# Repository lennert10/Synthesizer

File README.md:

# Synthesizer
Analog synthesizer top level repository

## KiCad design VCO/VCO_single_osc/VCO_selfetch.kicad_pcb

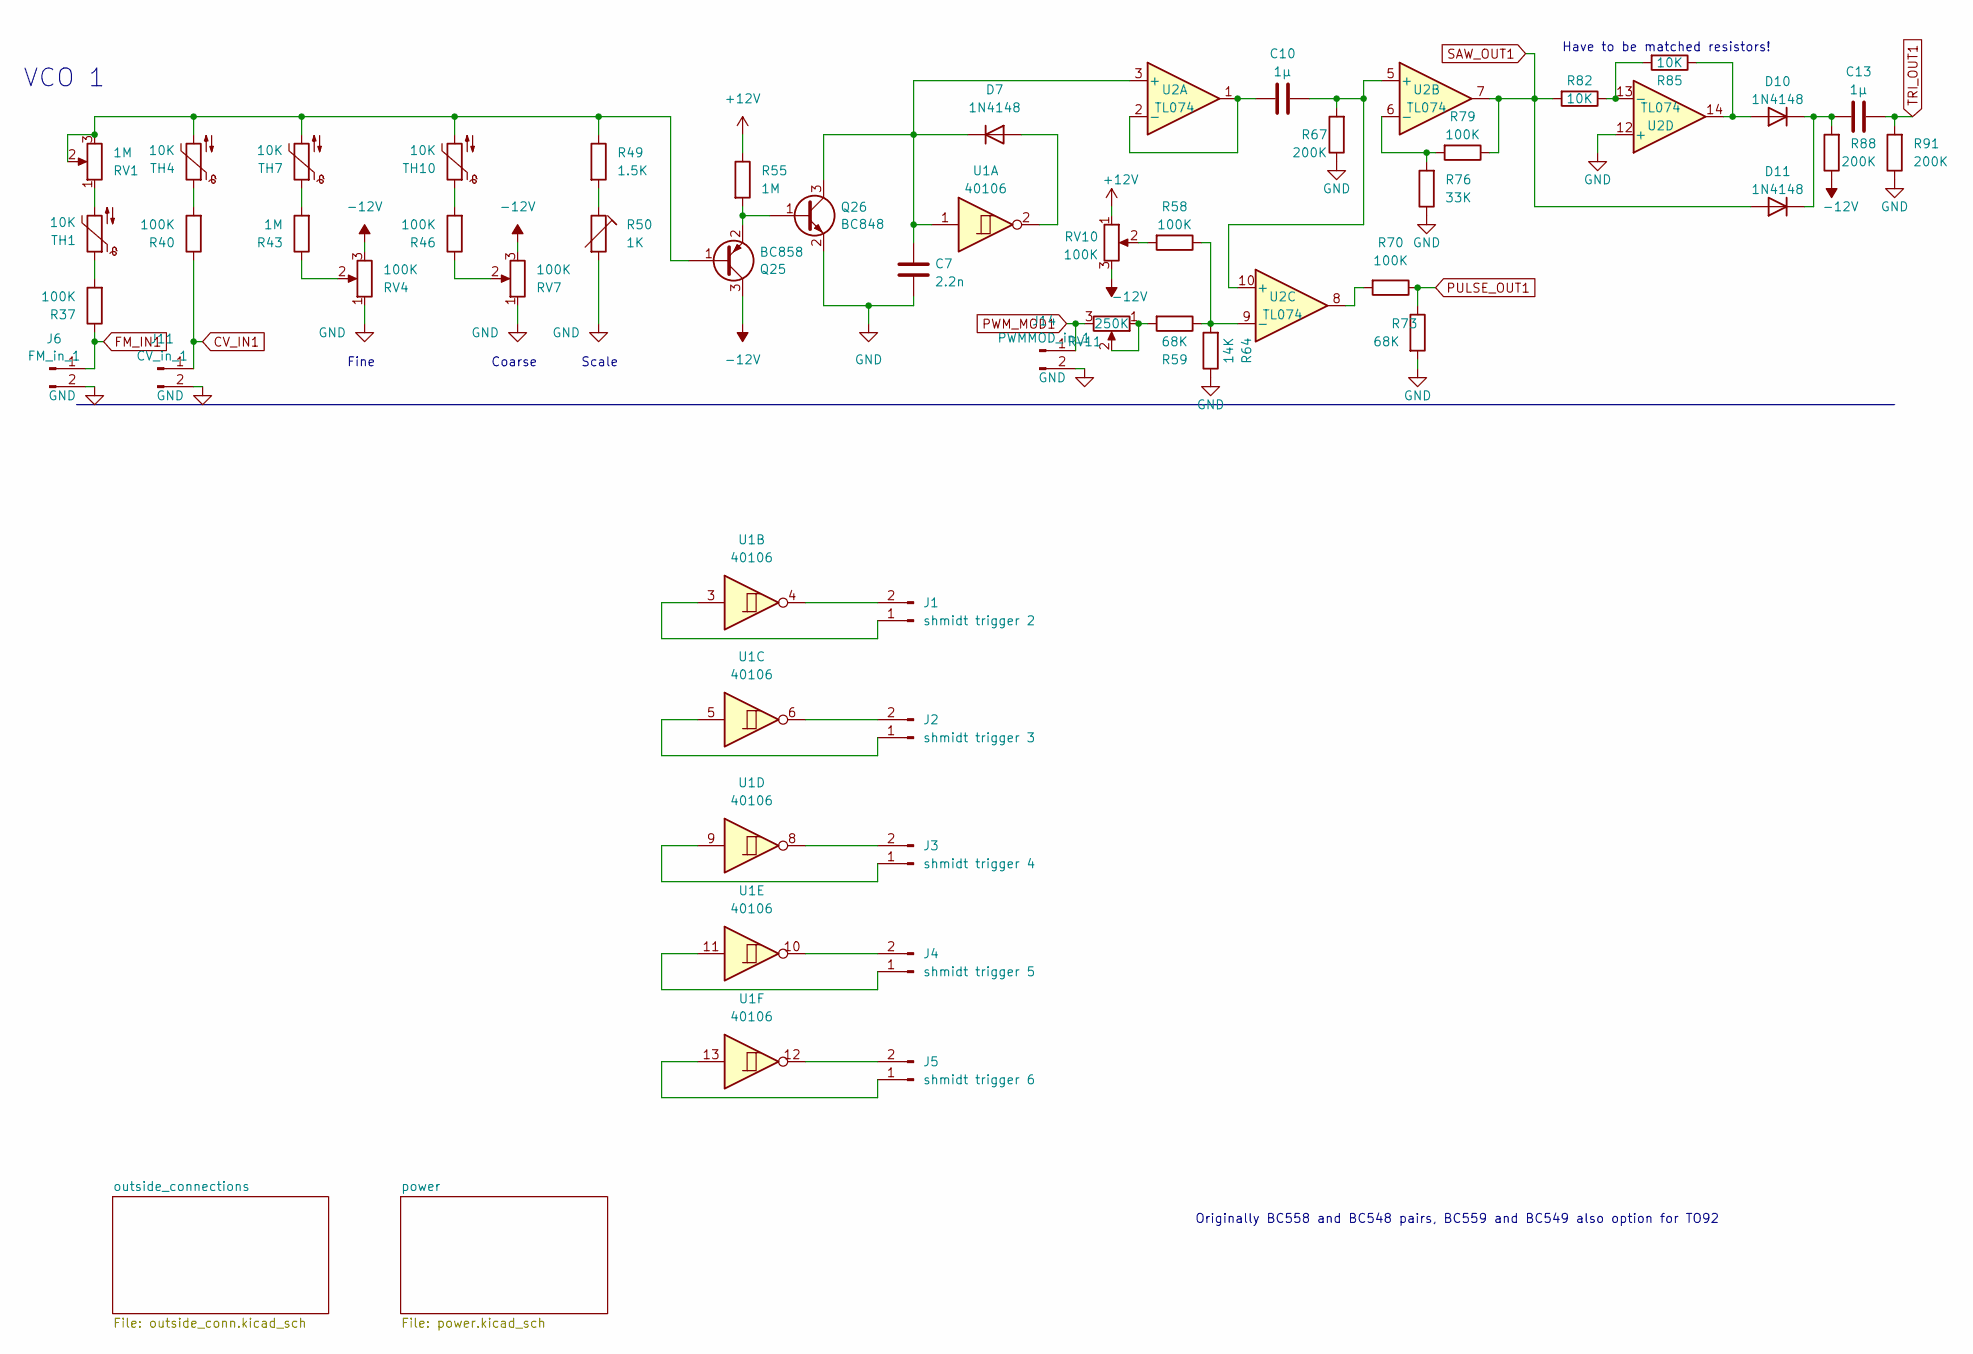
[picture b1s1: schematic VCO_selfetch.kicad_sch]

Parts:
C7: 2.2n; C_0402_1005Metric_Pad0.74x0.62mm_HandSolder
C10, C13: 1µ; C_0402_1005Metric_Pad0.74x0.62mm_HandSolder
D7, D10, D11: 1N4148; D_SOD-123
J1: shmidt trigger 2; PinHeader_1x02_P2.00mm_Vertical
J2: shmidt trigger 3; PinHeader_1x02_P2.00mm_Vertical
J3: shmidt trigger 4; PinHeader_1x02_P2.00mm_Vertical
J4: shmidt trigger 5; PinHeader_1x02_P2.00mm_Vertical
J5: shmidt trigger 6; PinHeader_1x02_P2.00mm_Vertical
J6: FM_in_1; PinHeader_1x02_P2.54mm_Vertical
J11: CV_in_1; PinHeader_1x02_P2.54mm_Vertical
J14: PWMMOD_in_1; PinHeader_1x02_P2.54mm_Vertical
Q25: BC858; SOT-23
Q26: BC848; SOT-23
R37, R40, R46, R58, R70, R79: 100K; R_0603_1608Metric_Pad0.98x0.95mm_HandSolder
R43, R55: 1M; R_0603_1608Metric_Pad0.98x0.95mm_HandSolder
R49: 1.5K; R_0603_1608Metric_Pad0.98x0.95mm_HandSolder
R50: 1K; Potentiometer_Bourns_3296W_Vertical
R59, R73: 68K; R_0603_1608Metric_Pad0.98x0.95mm_HandSolder
R64: 14K; R_0603_1608Metric_Pad0.98x0.95mm_HandSolder
R67, R88, R91: 200K; R_0603_1608Metric_Pad0.98x0.95mm_HandSolder
R76: 33K; R_0603_1608Metric_Pad0.98x0.95mm_HandSolder
R82, R85: 10K; R_0603_1608Metric_Pad0.98x0.95mm_HandSolder
RV1: 1M; PinHeader_1x03_P2.54mm_Vertical
RV4, RV7, RV10: 100K; PinHeader_1x03_P2.54mm_Vertical
RV11: 250K; PinHeader_1x03_P2.54mm_Vertical
TH1, TH4, TH7, TH10: 10K; R_0603_1608Metric_Pad0.98x0.95mm_HandSolder
U1: 40106; DIP-14_W7.62mm_Socket
U2: TL074; DIP-14_W7.62mm_Socket

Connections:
+12V: R55.1, RV10.1; also elsewhere on the board
-12V: Q25.3 (C), R88.1, RV4.3, RV7.3, RV10.3; also elsewhere on the board
CV_IN1: J11.1, R40.1
FM_IN1: J6.1, R37.1
GND: C7.1, J6.2, J11.2, J14.2, Q26.2 (E), R50.2, R64.1, R67.1, R73.2, R76.1, R91.1, RV4.1, RV7.1, U2.12 (+); also elsewhere on the board
unnamed: D7.2 (A), U1.2
unnamed: C7.2, D7.1 (K), Q26.3 (C), U1.1, U2.3 (+)
unnamed: D10.2 (A), R85.1, U2.14
unnamed: C13.2, D10.1 (K), D11.1 (K), R88.2
unnamed: J1.1, U1.3
unnamed: J1.2, U1.4
unnamed: J2.1, U1.5
unnamed: J2.2, U1.6
unnamed: J3.1, U1.9
unnamed: J3.2, U1.8
unnamed: J4.1, U1.11
unnamed: J4.2, U1.10
unnamed: J5.1, U1.13
unnamed: J5.2, U1.12
unnamed: Q25.1 (B), R49.1, RV1.2, RV1.3, TH4.2, TH7.2, TH10.2
unnamed: Q25.2 (E), Q26.1 (B), R55.2
unnamed: R37.2, TH1.1
unnamed: R40.2, TH4.1
unnamed: R43.1, RV4.2
unnamed: R43.2, TH7.1
unnamed: R46.1, RV7.2
unnamed: R46.2, TH10.1
unnamed: R49.2, R50.1
unnamed: R58.2, RV10.2
unnamed: R59.2, RV11.1, RV11.2
unnamed: R70.2, U2.8
unnamed: RV1.1, TH1.2
unnamed: C10.2, U2.1, U2.2 (-)
unnamed: C10.1, R67.2, U2.5 (+), U2.10 (+)
unnamed: R76.2, R79.2, U2.6 (-)
unnamed: R58.1, R59.1, R64.2, U2.9 (-)
unnamed: R82.1, R85.2, U2.13 (-)
PULSE_OUT1: R70.1, R73.1; also elsewhere on the board
PWM_MOD1: J14.1, RV11.3
SAW_OUT1: D11.2 (A), R79.1, R82.2, U2.7; also elsewhere on the board
TRI_OUT1: C13.1, R91.2; also elsewhere on the board

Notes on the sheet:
Have to be matched resistors!
Fine
VCO 1
Coarse
Scale
Originally BC558 and BC548 pairs, BC559 and BC549 also option for TO92

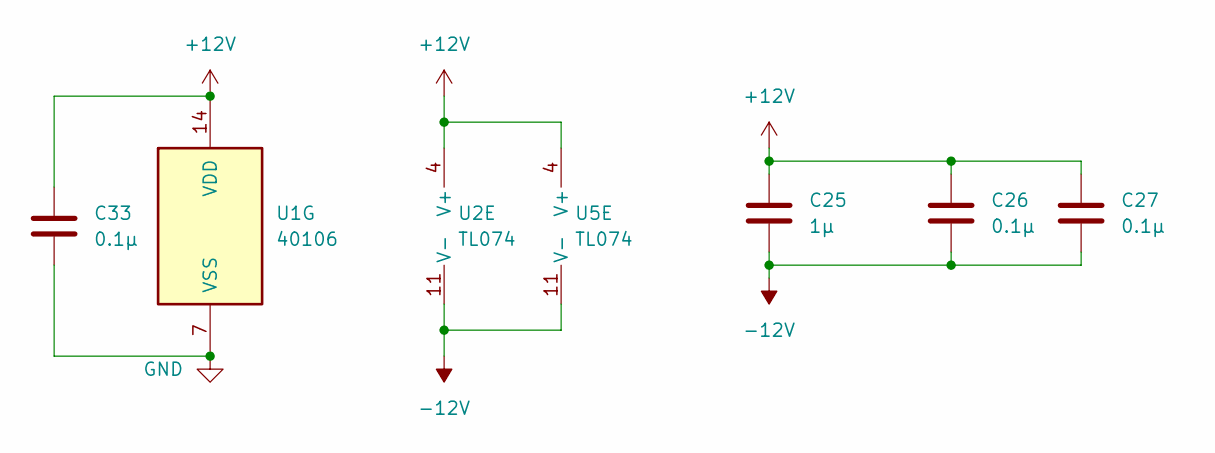
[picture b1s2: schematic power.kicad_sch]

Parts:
C25: 1µ; C_0402_1005Metric_Pad0.74x0.62mm_HandSolder
C26, C27, C33: 0.1µ; C_0603_1608Metric_Pad1.08x0.95mm_HandSolder
U1: 40106; DIP-14_W7.62mm_Socket
U2, U5: TL074; DIP-14_W7.62mm_Socket

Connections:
+12V: C25.2, C26.2, C27.2, C33.2, U1.14 (VDD), U2.4 (V+), U5.4 (V+); also elsewhere on the board
-12V: C25.1, C26.1, C27.1, U2.11 (V-), U5.11 (V-); also elsewhere on the board
GND: C33.1, U1.7 (VSS); also elsewhere on the board

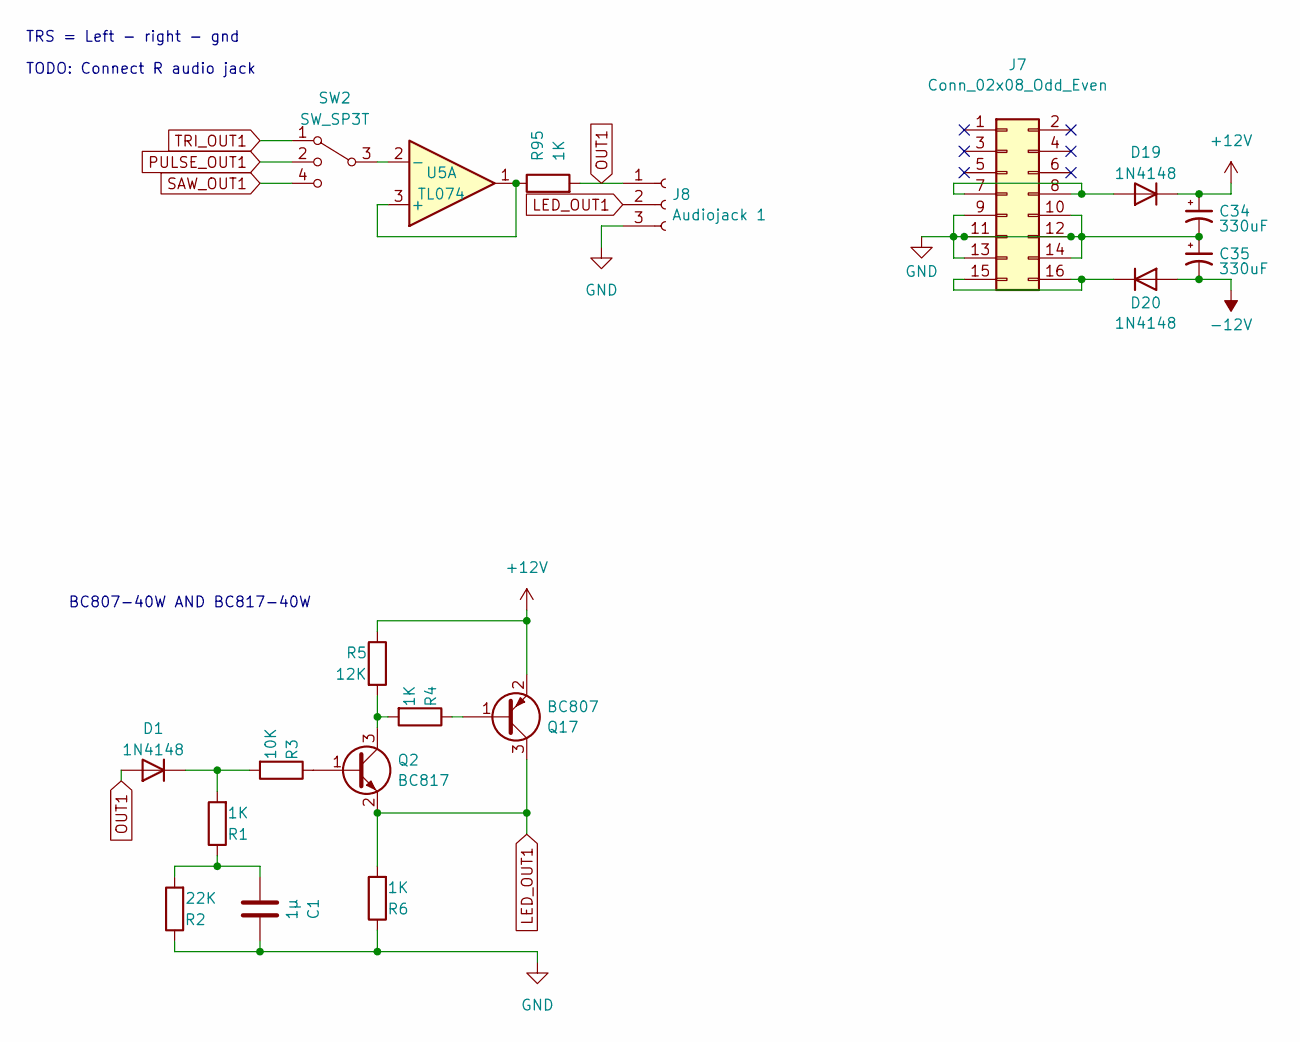
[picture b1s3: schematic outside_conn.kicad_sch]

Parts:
C1: 1µ; C_0402_1005Metric_Pad0.74x0.62mm_HandSolder
C34, C35: 330uF; CP_Radial_D12.5mm_P7.50mm
D1, D19, D20: 1N4148; D_SOD-123
J7: Conn_02x08_Odd_Even; PinHeader_2x08_P2.54mm_Vertical
J8: Audiojack 1; PinHeader_1x03_P2.54mm_Vertical
Q2: BC817; SOT-23
Q17: BC807; SOT-23
R1, R4, R6, R95: 1K; R_0603_1608Metric_Pad0.98x0.95mm_HandSolder
R2: 22K; R_0603_1608Metric_Pad0.98x0.95mm_HandSolder
R3: 10K; R_0603_1608Metric_Pad0.98x0.95mm_HandSolder
R5: 12K; R_0603_1608Metric_Pad0.98x0.95mm_HandSolder
SW2: SW_SP3T; PinHeader_1x04_P2.54mm_Vertical
U5: TL074; DIP-14_W7.62mm_Socket

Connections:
+12V: C34.1, D19.1 (K), Q17.2 (E), R5.1; also elsewhere on the board
-12V: C35.2, D20.2 (A); also elsewhere on the board
GND: C1.1, C34.2, C35.1, J7.9, J7.10, J7.11, J7.12, J7.13, J7.14, J8.3, R2.1, R6.1; also elsewhere on the board
LED_OUT1: J8.2, Q2.2 (E), Q17.3 (C), R6.2
unnamed: C1.2, R1.1, R2.2
unnamed: D1.1 (K), R1.2, R3.2
unnamed: D19.2 (A), J7.7, J7.8
unnamed: D20.1 (K), J7.15, J7.16
unnamed: Q2.1 (B), R3.1
unnamed: Q2.3 (C), R4.2, R5.2
unnamed: Q17.1 (B), R4.1
unnamed: R95.1, U5.1, U5.3 (+)
unnamed: SW2.3, U5.2 (-)
OUT1: D1.2 (A), J8.1, R95.2
PULSE_OUT1: SW2.2; also elsewhere on the board
SAW_OUT1: SW2.4; also elsewhere on the board
TRI_OUT1: SW2.1; also elsewhere on the board

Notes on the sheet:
TRS = Left - right - gnd
BC807-40W AND BC817-40W
TODO: Connect R audio jack

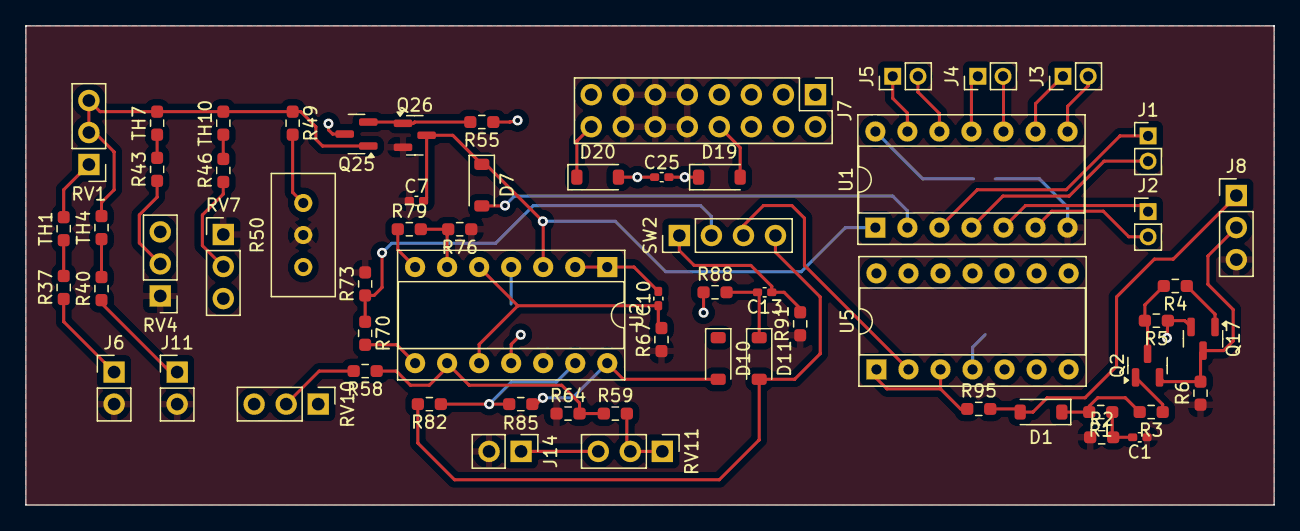
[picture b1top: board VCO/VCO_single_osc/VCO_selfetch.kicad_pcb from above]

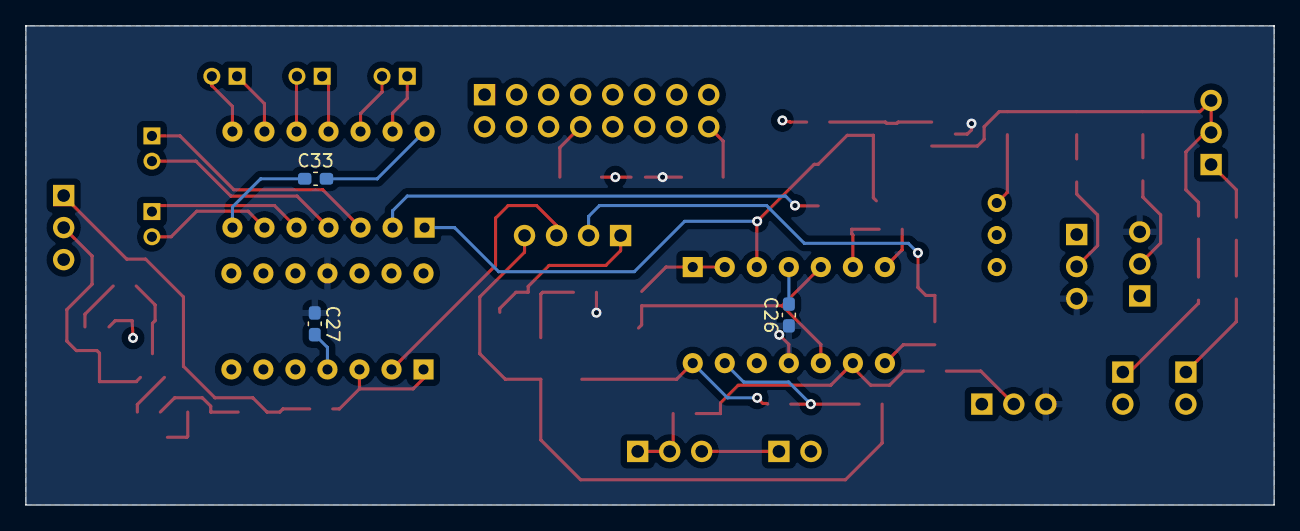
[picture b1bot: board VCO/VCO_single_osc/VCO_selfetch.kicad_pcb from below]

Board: 4 copper layers, 99.0 x 38.0 mm, 67 parts (3 on the bottom side), 52 nets.

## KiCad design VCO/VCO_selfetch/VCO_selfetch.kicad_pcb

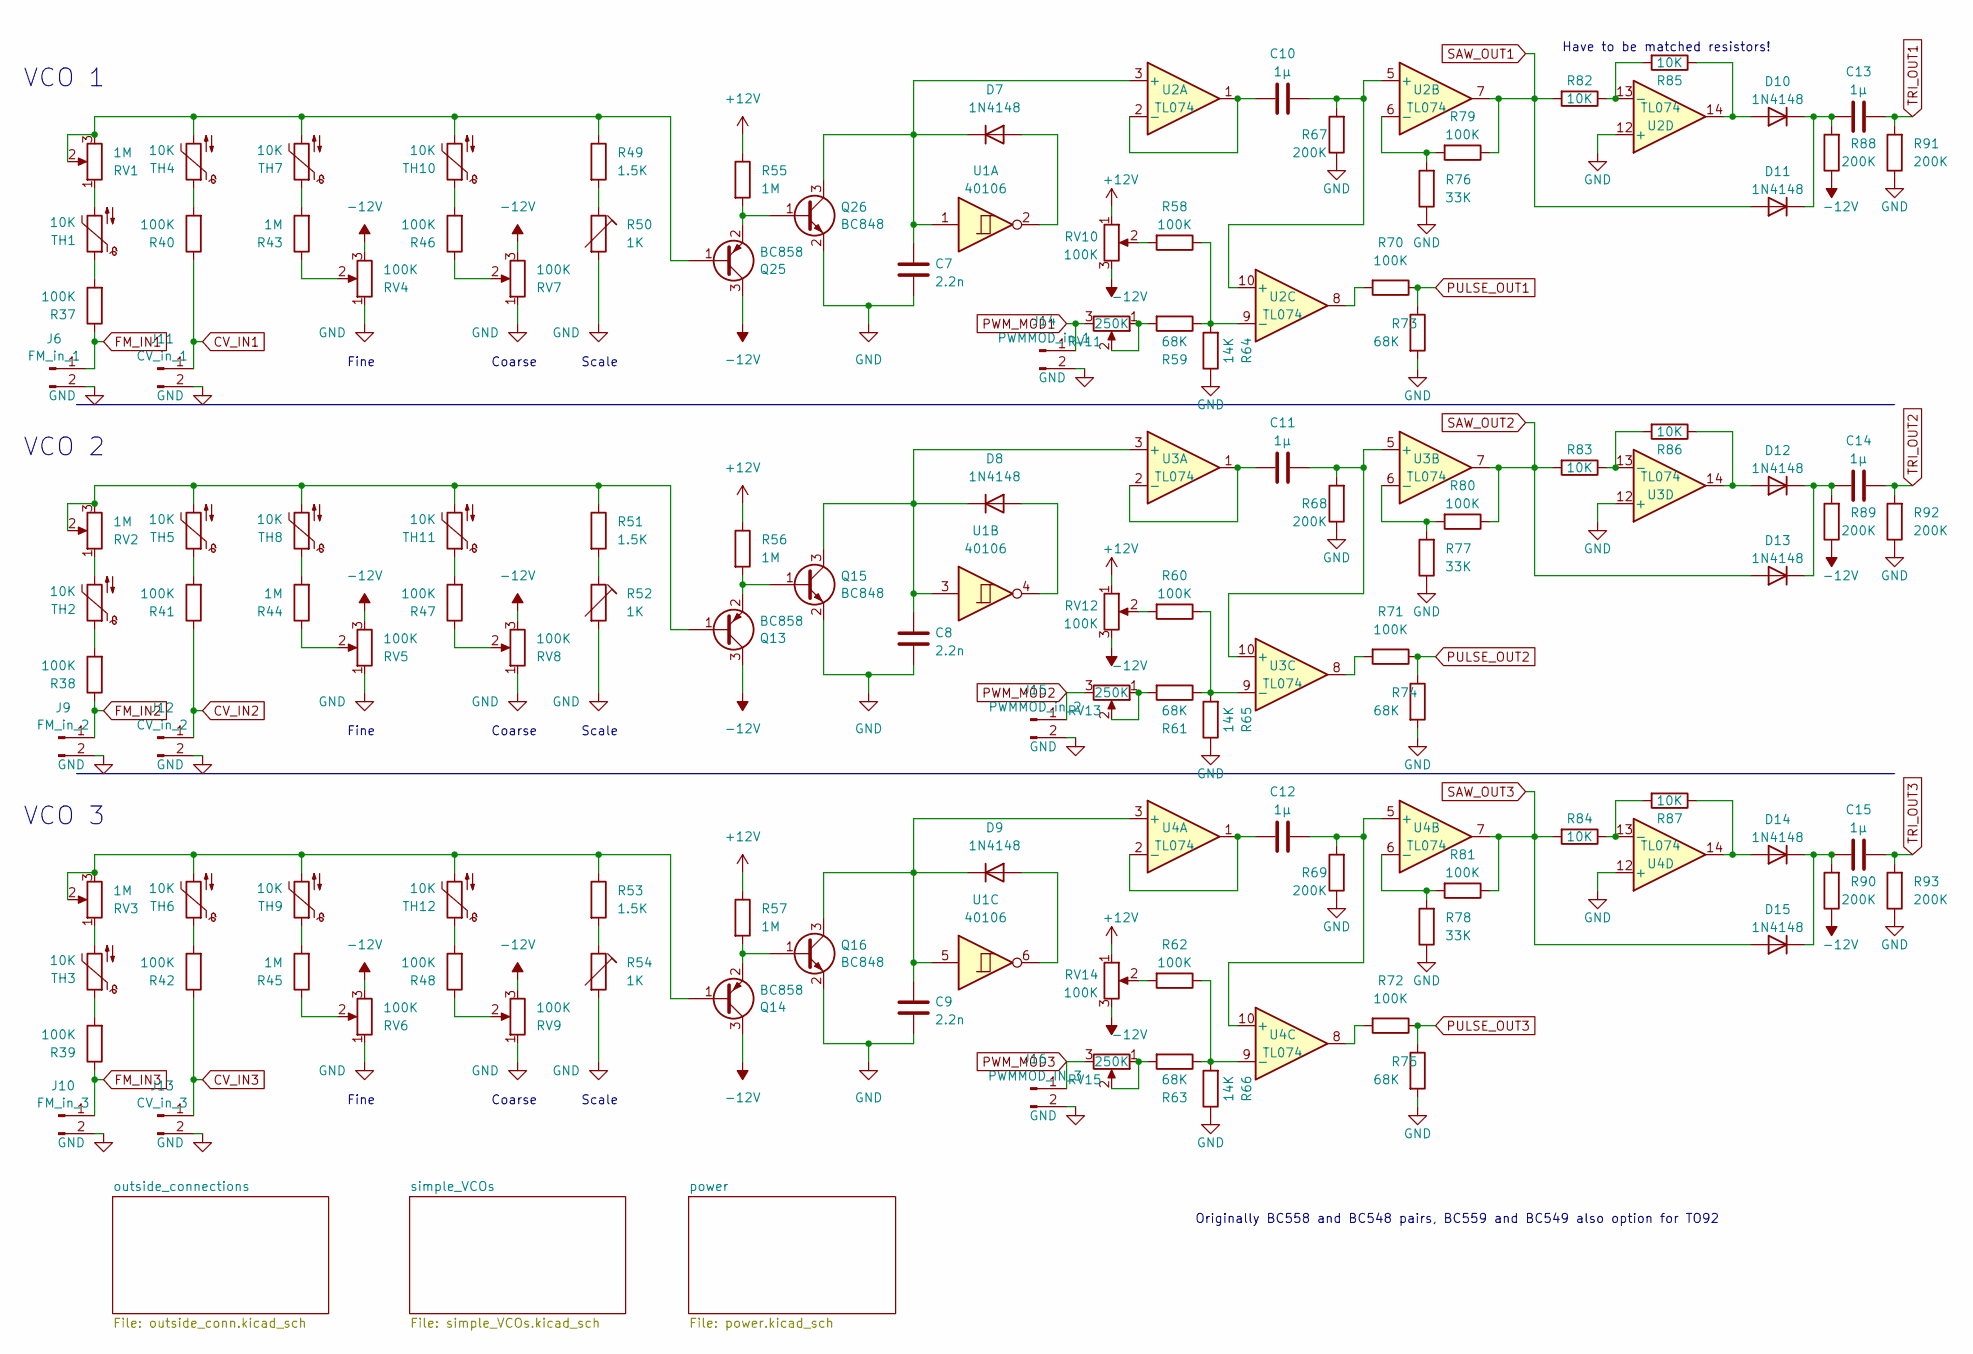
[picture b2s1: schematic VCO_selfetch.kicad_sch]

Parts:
C7, C8, C9: 2.2n; C_0402_1005Metric_Pad0.74x0.62mm_HandSolder
C10, C11, C12, C13, C14, C15: 1µ; C_0402_1005Metric_Pad0.74x0.62mm_HandSolder
D7, D8, D9, D10, D11, D12, D13, D14, D15: 1N4148; D_SOD-123
J6: FM_in_1; PinHeader_1x02_P2.54mm_Vertical
J9: FM_in_2; PinHeader_1x02_P2.54mm_Vertical
J10: FM_in_3; PinHeader_1x02_P2.54mm_Vertical
J11: CV_in_1; PinHeader_1x02_P2.54mm_Vertical
J12: CV_in_2; PinHeader_1x02_P2.54mm_Vertical
J13: CV_in_3; PinHeader_1x02_P2.54mm_Vertical
J14: PWMMOD_in_1; PinHeader_1x02_P2.54mm_Vertical
J15: PWMMOD_in_2; PinHeader_1x02_P2.54mm_Vertical
J16: PWMMOD_IN_3; PinHeader_1x02_P2.54mm_Vertical
Q13, Q14, Q25: BC858; SOT-23
Q15, Q16, Q26: BC848; SOT-23
R37, R38, R39, R40, R41, R42, R46, R47, R48, R58, R60, R62, R70, R71, R72, R79, R80, R81: 100K; R_0603_1608Metric_Pad0.98x0.95mm_HandSolder
R43, R44, R45, R55, R56, R57: 1M; R_0603_1608Metric_Pad0.98x0.95mm_HandSolder
R49, R51, R53: 1.5K; R_0603_1608Metric_Pad0.98x0.95mm_HandSolder
R50, R52, R54: 1K; Potentiometer_Bourns_3296W_Vertical
R59, R61, R63, R73, R74, R75: 68K; R_0603_1608Metric_Pad0.98x0.95mm_HandSolder
R64, R65, R66: 14K; R_0603_1608Metric_Pad0.98x0.95mm_HandSolder
R67, R68, R69, R88, R89, R90, R91, R92, R93: 200K; R_0603_1608Metric_Pad0.98x0.95mm_HandSolder
R76, R77, R78: 33K; R_0603_1608Metric_Pad0.98x0.95mm_HandSolder
R82, R83, R84, R85, R86, R87: 10K; R_0603_1608Metric_Pad0.98x0.95mm_HandSolder
RV1, RV2, RV3: 1M; PinHeader_1x03_P2.54mm_Vertical
RV4, RV5, RV6, RV7, RV8, RV9, RV10, RV12, RV14: 100K; PinHeader_1x03_P2.54mm_Vertical
RV11, RV13, RV15: 250K; PinHeader_1x03_P2.54mm_Vertical
TH1, TH2, TH3, TH4, TH5, TH6, TH7, TH8, TH9, TH10, TH11, TH12: 10K; R_0603_1608Metric_Pad0.98x0.95mm_HandSolder
U1: 40106; DIP-14_W7.62mm_Socket
U2, U3, U4: TL074; DIP-14_W7.62mm_Socket

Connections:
+12V: R55.1, R56.1, R57.1, RV10.1, RV12.1, RV14.1; also elsewhere on the board
-12V: Q13.3 (C), Q14.3 (C), Q25.3 (C), R88.1, R89.1, R90.1, RV4.3, RV5.3, RV6.3, RV7.3, RV8.3, RV9.3, RV10.3, RV12.3, RV14.3; also elsewhere on the board
CV_IN1: J11.1, R40.1
CV_IN2: J12.1, R41.1
CV_IN3: J13.1, R42.1
FM_IN1: J6.1, R37.1
FM_IN2: J9.1, R38.1
FM_IN3: J10.1, R39.1
GND: C7.1, C8.1, C9.1, J6.2, J9.2, J10.2, J11.2, J12.2, J13.2, J14.2, J15.2, J16.2, Q15.2 (E), Q16.2 (E), Q26.2 (E), R50.2, R52.2, R54.2, R64.1, R65.1, R66.1, R67.1, R68.1, R69.1, R73.2, R74.2, R75.2, R76.1, R77.1, R78.1, R91.1, R92.1, R93.1, RV4.1, RV5.1, RV6.1, RV7.1, RV8.1, RV9.1, U2.12 (+), U3.12 (+), U4.12 (+); also elsewhere on the board
unnamed: D7.2 (A), U1.2
unnamed: C7.2, D7.1 (K), Q26.3 (C), U1.1, U2.3 (+)
unnamed: D8.2 (A), U1.4
unnamed: C8.2, D8.1 (K), Q15.3 (C), U1.3, U3.3 (+)
unnamed: D9.2 (A), U1.6
unnamed: C9.2, D9.1 (K), Q16.3 (C), U1.5, U4.3 (+)
unnamed: D10.2 (A), R85.1, U2.14
unnamed: C13.2, D10.1 (K), D11.1 (K), R88.2
unnamed: D12.2 (A), R86.1, U3.14
unnamed: C14.2, D12.1 (K), D13.1 (K), R89.2
unnamed: D14.2 (A), R87.1, U4.14
unnamed: C15.2, D14.1 (K), D15.1 (K), R90.2
unnamed: Q13.1 (B), R51.1, RV2.2, RV2.3, TH5.2, TH8.2, TH11.2
unnamed: Q13.2 (E), Q15.1 (B), R56.2
unnamed: Q14.1 (B), R53.1, RV3.2, RV3.3, TH6.2, TH9.2, TH12.2
unnamed: Q14.2 (E), Q16.1 (B), R57.2
unnamed: Q25.1 (B), R49.1, RV1.2, RV1.3, TH4.2, TH7.2, TH10.2
unnamed: Q25.2 (E), Q26.1 (B), R55.2
unnamed: R37.2, TH1.1
unnamed: R38.2, TH2.1
unnamed: R39.2, TH3.1
unnamed: R40.2, TH4.1
unnamed: R41.2, TH5.1
unnamed: R42.2, TH6.1
unnamed: R43.1, RV4.2
unnamed: R43.2, TH7.1
unnamed: R44.1, RV5.2
unnamed: R44.2, TH8.1
unnamed: R45.1, RV6.2
unnamed: R45.2, TH9.1
unnamed: R46.1, RV7.2
unnamed: R46.2, TH10.1
unnamed: R47.1, RV8.2
unnamed: R47.2, TH11.1
unnamed: R48.1, RV9.2
unnamed: R48.2, TH12.1
unnamed: R49.2, R50.1
unnamed: R51.2, R52.1
unnamed: R53.2, R54.1
unnamed: R58.2, RV10.2
unnamed: R59.2, RV11.1, RV11.2
unnamed: R60.2, RV12.2
unnamed: R61.2, RV13.1, RV13.2
unnamed: R62.2, RV14.2
unnamed: R63.2, RV15.1, RV15.2
unnamed: R70.2, U2.8
unnamed: R71.2, U3.8
unnamed: R72.2, U4.8
unnamed: RV1.1, TH1.2
unnamed: RV2.1, TH2.2
unnamed: RV3.1, TH3.2
unnamed: C10.2, U2.1, U2.2 (-)
unnamed: C10.1, R67.2, U2.5 (+), U2.10 (+)
unnamed: R76.2, R79.2, U2.6 (-)
unnamed: R58.1, R59.1, R64.2, U2.9 (-)
unnamed: R82.1, R85.2, U2.13 (-)
unnamed: C11.2, U3.1, U3.2 (-)
unnamed: C11.1, R68.2, U3.5 (+), U3.10 (+)
unnamed: R77.2, R80.2, U3.6 (-)
unnamed: R60.1, R61.1, R65.2, U3.9 (-)
unnamed: R83.1, R86.2, U3.13 (-)
unnamed: C12.2, U4.1, U4.2 (-)
unnamed: C12.1, R69.2, U4.5 (+), U4.10 (+)
unnamed: R78.2, R81.2, U4.6 (-)
unnamed: R62.1, R63.1, R66.2, U4.9 (-)
unnamed: R84.1, R87.2, U4.13 (-)
PULSE_OUT1: R70.1, R73.1; also elsewhere on the board
PULSE_OUT2: R71.1, R74.1; also elsewhere on the board
PULSE_OUT3: R72.1, R75.1; also elsewhere on the board
PWM_MOD1: J14.1, RV11.3
PWM_MOD2: J15.1, RV13.3
PWM_MOD3: J16.1, RV15.3
SAW_OUT1: D11.2 (A), R79.1, R82.2, U2.7; also elsewhere on the board
SAW_OUT2: D13.2 (A), R80.1, R83.2, U3.7; also elsewhere on the board
SAW_OUT3: D15.2 (A), R81.1, R84.2, U4.7; also elsewhere on the board
TRI_OUT1: C13.1, R91.2; also elsewhere on the board
TRI_OUT2: C14.1, R92.2; also elsewhere on the board
TRI_OUT3: C15.1, R93.2; also elsewhere on the board

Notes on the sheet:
Coarse
VCO 2
Scale
Fine
Have to be matched resistors!
VCO 1
VCO 3
Originally BC558 and BC548 pairs, BC559 and BC549 also option for TO92

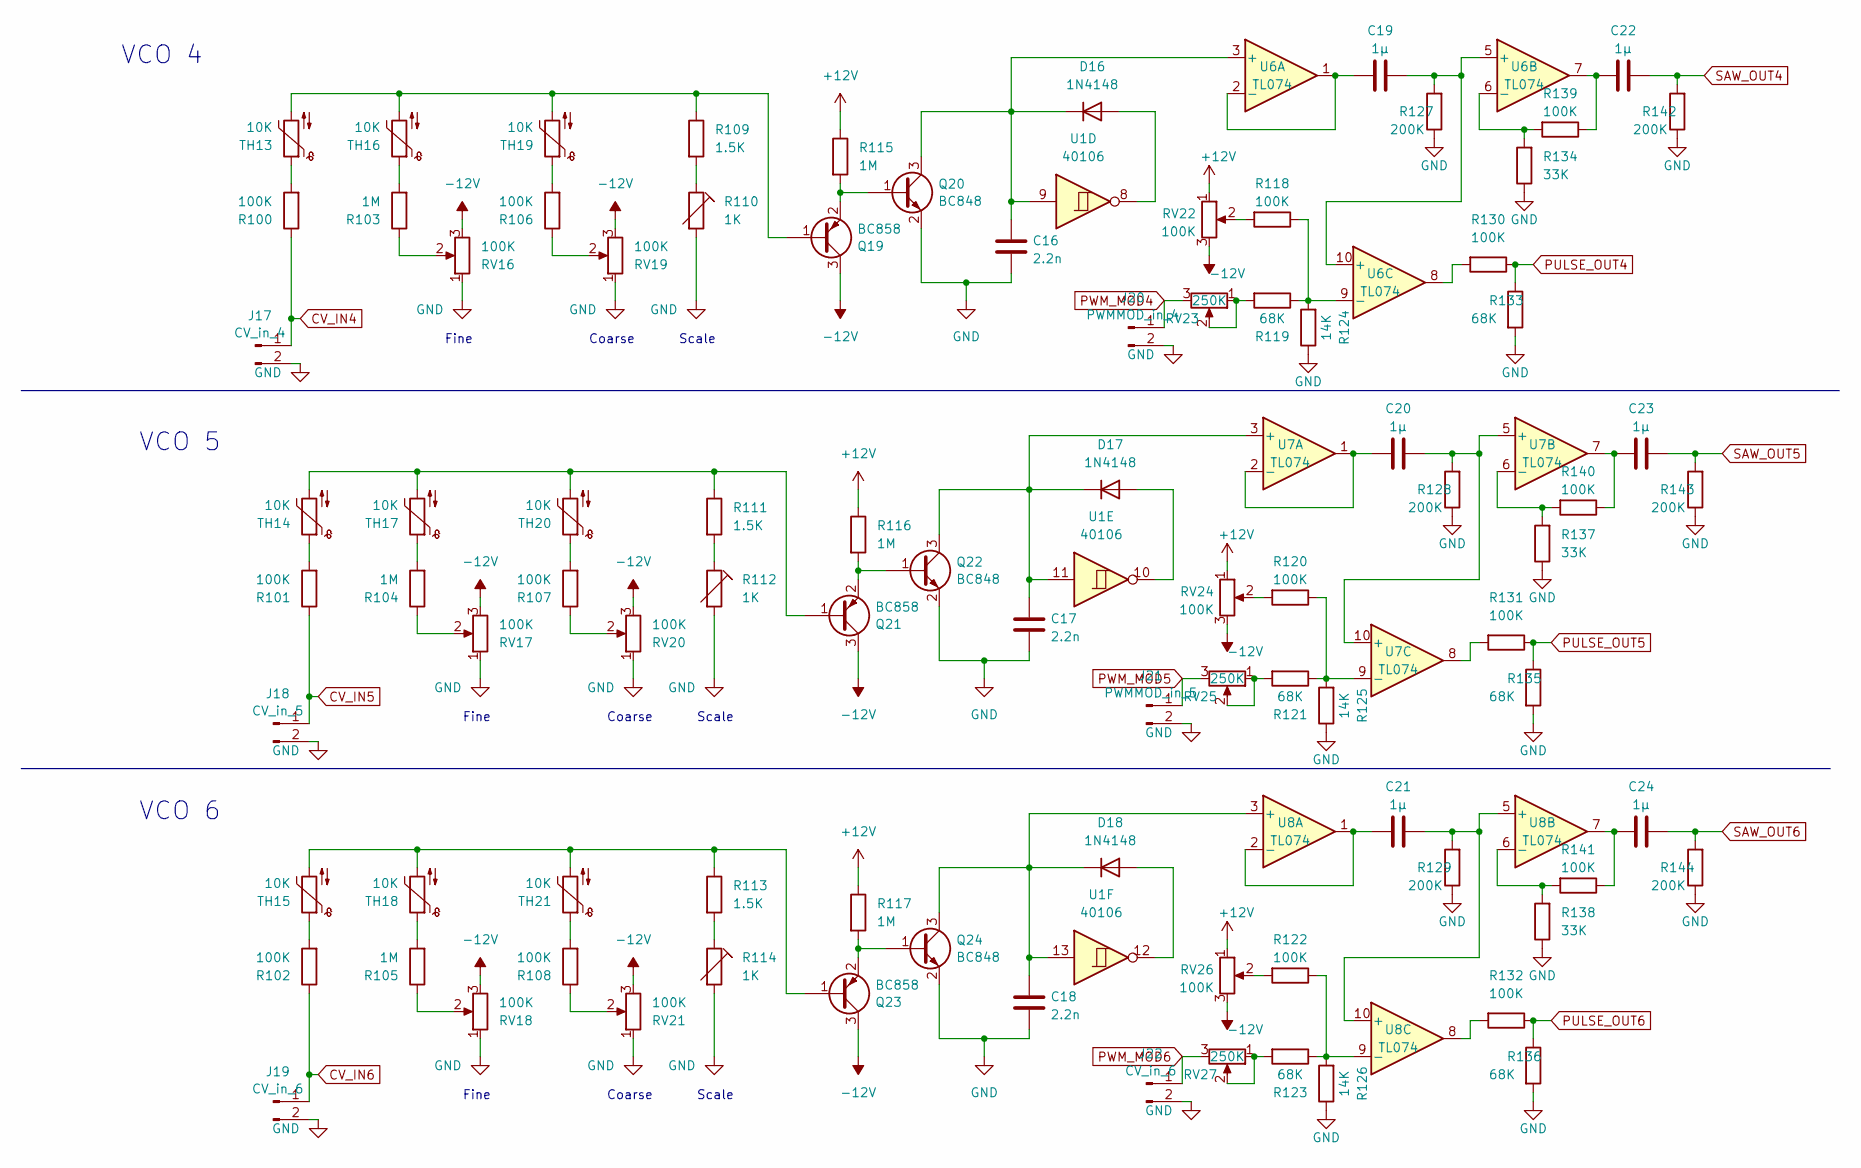
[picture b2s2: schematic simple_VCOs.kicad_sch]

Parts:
C16, C17, C18: 2.2n; C_0402_1005Metric_Pad0.74x0.62mm_HandSolder
C19, C20, C21, C22, C23, C24: 1µ; C_0402_1005Metric_Pad0.74x0.62mm_HandSolder
D16, D17, D18: 1N4148; D_SOD-123
J17: CV_in_4; PinHeader_1x02_P2.54mm_Vertical
J18: CV_in_5; PinHeader_1x02_P2.54mm_Vertical
J19, J22: CV_in_6; PinHeader_1x02_P2.54mm_Vertical
J20: PWMMOD_in_4; PinHeader_1x02_P2.54mm_Vertical
J21: PWMMOD_in_5; PinHeader_1x02_P2.54mm_Vertical
Q19, Q21, Q23: BC858; SOT-23
Q20, Q22, Q24: BC848; SOT-23
R100, R101, R102, R106, R107, R108, R118, R120, R122, R130, R131, R132, R139, R140, R141: 100K; R_0603_1608Metric_Pad0.98x0.95mm_HandSolder
R103, R104, R105, R115, R116, R117: 1M; R_0603_1608Metric_Pad0.98x0.95mm_HandSolder
R109, R111, R113: 1.5K; R_0603_1608Metric_Pad0.98x0.95mm_HandSolder
R110, R112, R114: 1K; Potentiometer_Bourns_3296W_Vertical
R119, R121, R123, R133, R135, R136: 68K; R_0603_1608Metric_Pad0.98x0.95mm_HandSolder
R124, R125, R126: 14K; R_0603_1608Metric_Pad0.98x0.95mm_HandSolder
R127, R128, R129, R142, R143, R144: 200K; R_0603_1608Metric_Pad0.98x0.95mm_HandSolder
R134, R137, R138: 33K; R_0603_1608Metric_Pad0.98x0.95mm_HandSolder
RV16, RV17, RV18, RV19, RV20, RV21, RV22, RV24, RV26: 100K; PinHeader_1x03_P2.54mm_Vertical
RV23, RV25, RV27: 250K; PinHeader_1x03_P2.54mm_Vertical
TH13, TH14, TH15, TH16, TH17, TH18, TH19, TH20, TH21: 10K; R_0603_1608Metric_Pad0.98x0.95mm_HandSolder
U1: 40106; DIP-14_W7.62mm_Socket
U6, U7, U8: TL074; DIP-14_W7.62mm_Socket

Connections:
+12V: R115.1, R116.1, R117.1, RV22.1, RV24.1, RV26.1; also elsewhere on the board
-12V: Q19.3 (C), Q21.3 (C), Q23.3 (C), RV16.3, RV17.3, RV18.3, RV19.3, RV20.3, RV21.3, RV22.3, RV24.3, RV26.3; also elsewhere on the board
CV_IN4: J17.1, R100.1
CV_IN5: J18.1, R101.1
CV_IN6: J19.1, R102.1
GND: C16.1, C17.1, C18.1, J17.2, J18.2, J19.2, J20.2, J21.2, J22.2, Q20.2 (E), Q22.2 (E), Q24.2 (E), R110.2, R112.2, R114.2, R124.1, R125.1, R126.1, R127.1, R128.1, R129.1, R133.2, R134.1, R135.2, R136.2, R137.1, R138.1, R142.1, R143.1, R144.1, RV16.1, RV17.1, RV18.1, RV19.1, RV20.1, RV21.1; also elsewhere on the board
unnamed: C22.2, R139.1, U6.7
unnamed: C23.2, R140.1, U7.7
unnamed: C24.2, R141.1, U8.7
unnamed: D16.2 (A), U1.8
unnamed: C16.2, D16.1 (K), Q20.3 (C), U1.9, U6.3 (+)
unnamed: D17.2 (A), U1.10
unnamed: C17.2, D17.1 (K), Q22.3 (C), U1.11, U7.3 (+)
unnamed: D18.2 (A), U1.12
unnamed: C18.2, D18.1 (K), Q24.3 (C), U1.13, U8.3 (+)
unnamed: Q19.1 (B), R109.1, TH13.2, TH16.2, TH19.2
unnamed: Q19.2 (E), Q20.1 (B), R115.2
unnamed: Q21.1 (B), R111.1, TH14.2, TH17.2, TH20.2
unnamed: Q21.2 (E), Q22.1 (B), R116.2
unnamed: Q23.1 (B), R113.1, TH15.2, TH18.2, TH21.2
unnamed: Q23.2 (E), Q24.1 (B), R117.2
unnamed: R100.2, TH13.1
unnamed: R101.2, TH14.1
unnamed: R102.2, TH15.1
unnamed: R103.1, RV16.2
unnamed: R103.2, TH16.1
unnamed: R104.1, RV17.2
unnamed: R104.2, TH17.1
unnamed: R105.1, RV18.2
unnamed: R105.2, TH18.1
unnamed: R106.1, RV19.2
unnamed: R106.2, TH19.1
unnamed: R107.1, RV20.2
unnamed: R107.2, TH20.1
unnamed: R108.1, RV21.2
unnamed: R108.2, TH21.1
unnamed: R109.2, R110.1
unnamed: R111.2, R112.1
unnamed: R113.2, R114.1
unnamed: R118.2, RV22.2
unnamed: R119.2, RV23.1, RV23.2
unnamed: R120.2, RV24.2
unnamed: R121.2, RV25.1, RV25.2
unnamed: R122.2, RV26.2
unnamed: R123.2, RV27.1, RV27.2
unnamed: R130.2, U6.8
unnamed: R131.2, U7.8
unnamed: R132.2, U8.8
unnamed: C19.2, U6.1, U6.2 (-)
unnamed: C19.1, R127.2, U6.5 (+), U6.10 (+)
unnamed: R134.2, R139.2, U6.6 (-)
unnamed: R118.1, R119.1, R124.2, U6.9 (-)
unnamed: C20.2, U7.1, U7.2 (-)
unnamed: C20.1, R128.2, U7.5 (+), U7.10 (+)
unnamed: R137.2, R140.2, U7.6 (-)
unnamed: R120.1, R121.1, R125.2, U7.9 (-)
unnamed: C21.2, U8.1, U8.2 (-)
unnamed: C21.1, R129.2, U8.5 (+), U8.10 (+)
unnamed: R138.2, R141.2, U8.6 (-)
unnamed: R122.1, R123.1, R126.2, U8.9 (-)
PULSE_OUT4: R130.1, R133.1; also elsewhere on the board
PULSE_OUT5: R131.1, R135.1; also elsewhere on the board
PULSE_OUT6: R132.1, R136.1; also elsewhere on the board
PWM_MOD4: J20.1, RV23.3
PWM_MOD5: J21.1, RV25.3
PWM_MOD6: J22.1, RV27.3
SAW_OUT4: C22.1, R142.2; also elsewhere on the board
SAW_OUT5: C23.1, R143.2; also elsewhere on the board
SAW_OUT6: C24.1, R144.2; also elsewhere on the board

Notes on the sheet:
Fine
Scale
VCO 6
Coarse
VCO 4
VCO 5

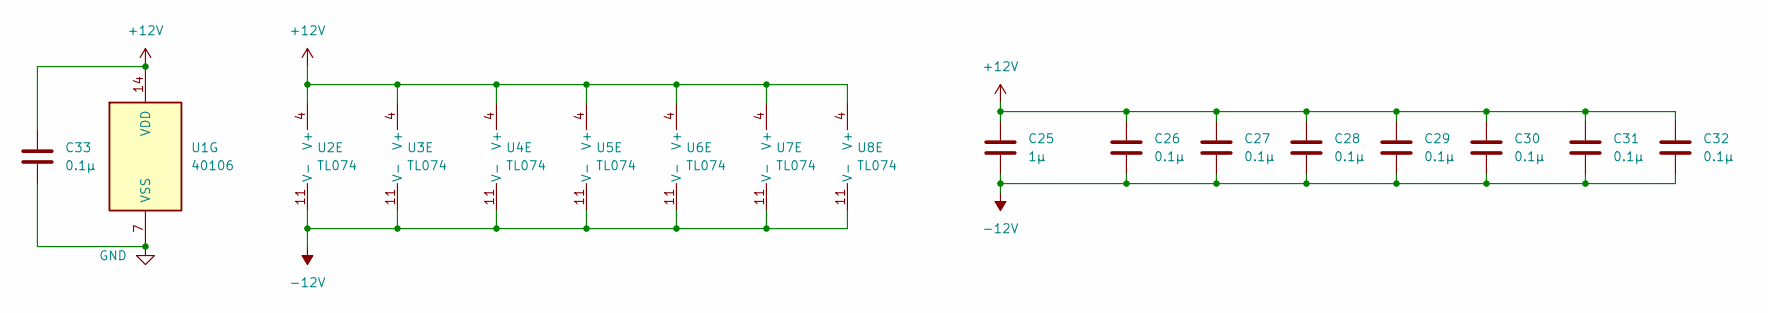
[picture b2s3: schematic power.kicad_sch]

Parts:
C25: 1µ; C_0402_1005Metric_Pad0.74x0.62mm_HandSolder
C26, C27, C28, C29, C30, C31, C32, C33: 0.1µ; C_0603_1608Metric_Pad1.08x0.95mm_HandSolder
U1: 40106; DIP-14_W7.62mm_Socket
U2, U3, U4, U5, U6, U7, U8: TL074; DIP-14_W7.62mm_Socket

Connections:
+12V: C25.2, C26.2, C27.2, C28.2, C29.2, C30.2, C31.2, C32.2, C33.2, U1.14 (VDD), U2.4 (V+), U3.4 (V+), U4.4 (V+), U5.4 (V+), U6.4 (V+), U7.4 (V+), U8.4 (V+); also elsewhere on the board
-12V: C25.1, C26.1, C27.1, C28.1, C29.1, C30.1, C31.1, C32.1, U2.11 (V-), U3.11 (V-), U4.11 (V-), U5.11 (V-), U6.11 (V-), U7.11 (V-), U8.11 (V-); also elsewhere on the board
GND: C33.1, U1.7 (VSS); also elsewhere on the board
